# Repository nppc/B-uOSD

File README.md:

# Battery voltage microOSD v1.2
Very small and simple OSD for monitoring Battery voltage. It is useful for AIO micro cameras, FPV helmet etc.

The PCB is very small. Can be ordered at OshPark: https://oshpark.com/shared_projects/nvOy0lBm

## Functionality
- Supports 1S-4S battery monitoring. (Changing onboard voltage divider can be extended for bigger batteries.)
- Adjustable text position.
- Shows current voltage and minimal detected voltage.
- Pilot name, Crosshair and timer.
- Voltage blinking if battery running low.
- Supply voltage 3.3-5.5v.
- Low supply current, no heat generation.
- It is very small size (8.8mm X 6mm).
- Virtually weights nothing.
- Configurable parameters via compiling.

It has minuses too.
- Due to small and slow mcu (no special mcu for signal generation) the OSD picture is not as stable as other bigger OSDs.
- No shadow around the symbols (not visible on white background). Planned it rhe future releases.

Discussion is here: https://www.rcgroups.com/forums/showthread.php?2985720-uOSD-World-smallest-micro-OSD

Some screenshots:

## Connection
There is many possibilities to use this OSD.
One example for 1S setup:

Another example for AIO combo camera/vtx 1S setup:

## Compilation
To compile source files there is several options.
### Under Linux (even cheap OrangePi board will work)
Install `avra` and `git`
```
apt-get install avra git
```
Clone the project to any directory
```
git clone https://github.com/nppc/B-uOSD.git
```
Navigate to `Bin` directory
```
cd B-uOSD/Bin
```
And run `compile_linux.sh` script
```
./compile_linux.sh
```
Now you have .hex file.

### Under Windows
Project can be compiled with AVRASM2 (similar to avra on Linux) or with AVR Studio.

## Flashing
Use `avrdude` software and `USBASP` dongle for flashing microcontroller. 

```
avrdude.exe -c usbasp -p t13 -P usb -B 4.0 -U flash:w:B-uOSD_vXX.hex:a
```

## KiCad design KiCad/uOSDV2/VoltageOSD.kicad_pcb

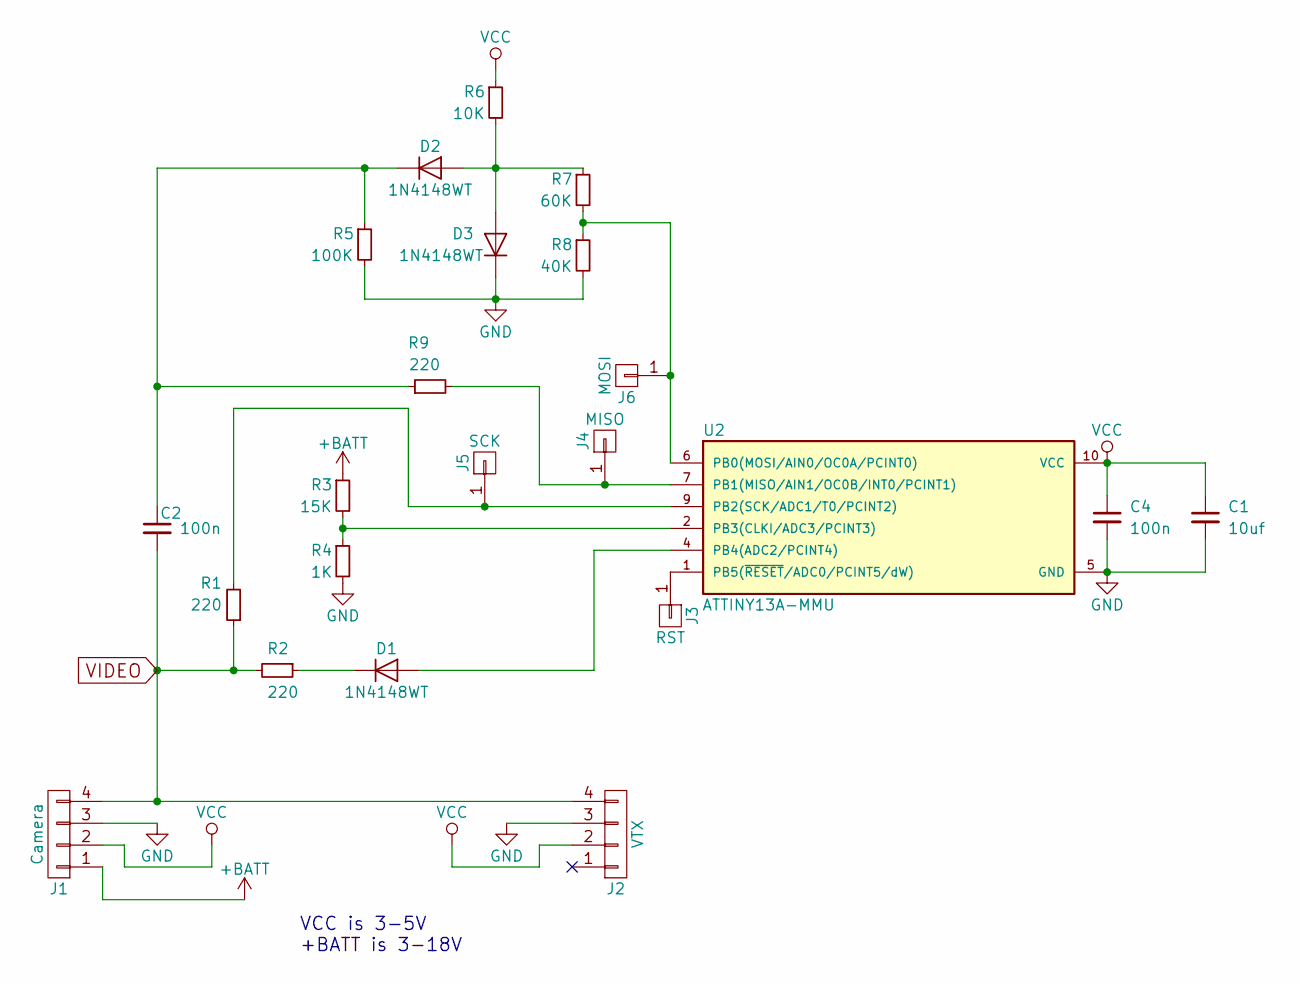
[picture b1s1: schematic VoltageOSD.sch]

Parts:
C1: 10uf; C_0402_NoSilk
C2, C4: 100n; C_0402_NoSilk
D1, D2, D3: 1N4148WT; D_SOD-523
J1: Camera; 4pin_SMD_small
J2: VTX; 4pin_SMD_small
J3: RST; Prog_pad
J4: MISO; Prog_pad
J5: SCK; Prog_pad
J6: MOSI; Prog_pad
R1, R2, R9: 220; R_0402_NoSilk
R3: 15K; R_0402_NoSilk
R4: 1K; R_0402_NoSilk
R5: 100K; R_0402_NoSilk
R6: 10K; R_0402_NoSilk
R7: 60K; R_0402_NoSilk
R8: 40K; R_0402_NoSilk
U2: ATTINY13A-MMU; MLF_10M1

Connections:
+BATT: J1.1, R3.1
GND: C1.2, C4.2, D3.1 (K), J1.3, J2.3, R4.2, R5.2, R8.2, U2.5 (GND)
unnamed: C2.1, D2.1 (K), R5.1, R9.1
unnamed: D1.1 (K), R2.1
unnamed: D1.2 (A), U2.4 (PB4(ADC2/PCINT4))
unnamed: D2.2 (A), D3.2 (A), R6.2, R7.1
unnamed: J3.1, U2.1 (PB5(~RESET~/ADC0/PCINT5/dW))
unnamed: J4.1, R9.2, U2.7 (PB1(MISO/AIN1/OC0B/INT0/PCINT1))
unnamed: J5.1, R1.2, U2.9 (PB2(SCK/ADC1/T0/PCINT2))
unnamed: J6.1, R7.2, R8.1, U2.6 (PB0(MOSI/AIN0/OC0A/PCINT0))
unnamed: R3.2, R4.1, U2.2 (PB3(CLKI/ADC3/PCINT3))
VCC: C1.1, C4.1, J1.2, J2.2, R6.1, U2.10 (VCC)
VIDEO: C2.2, J1.4, J2.4, R1.1, R2.2

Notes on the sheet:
VCC is 3-5V +BATT is 3-18V

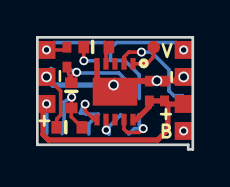
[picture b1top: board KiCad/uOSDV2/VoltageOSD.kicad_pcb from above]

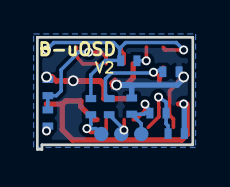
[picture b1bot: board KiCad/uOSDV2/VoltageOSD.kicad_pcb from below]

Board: 2 copper layers, 8.6 x 6.2 mm, 22 parts (12 on the bottom side), 13 nets.

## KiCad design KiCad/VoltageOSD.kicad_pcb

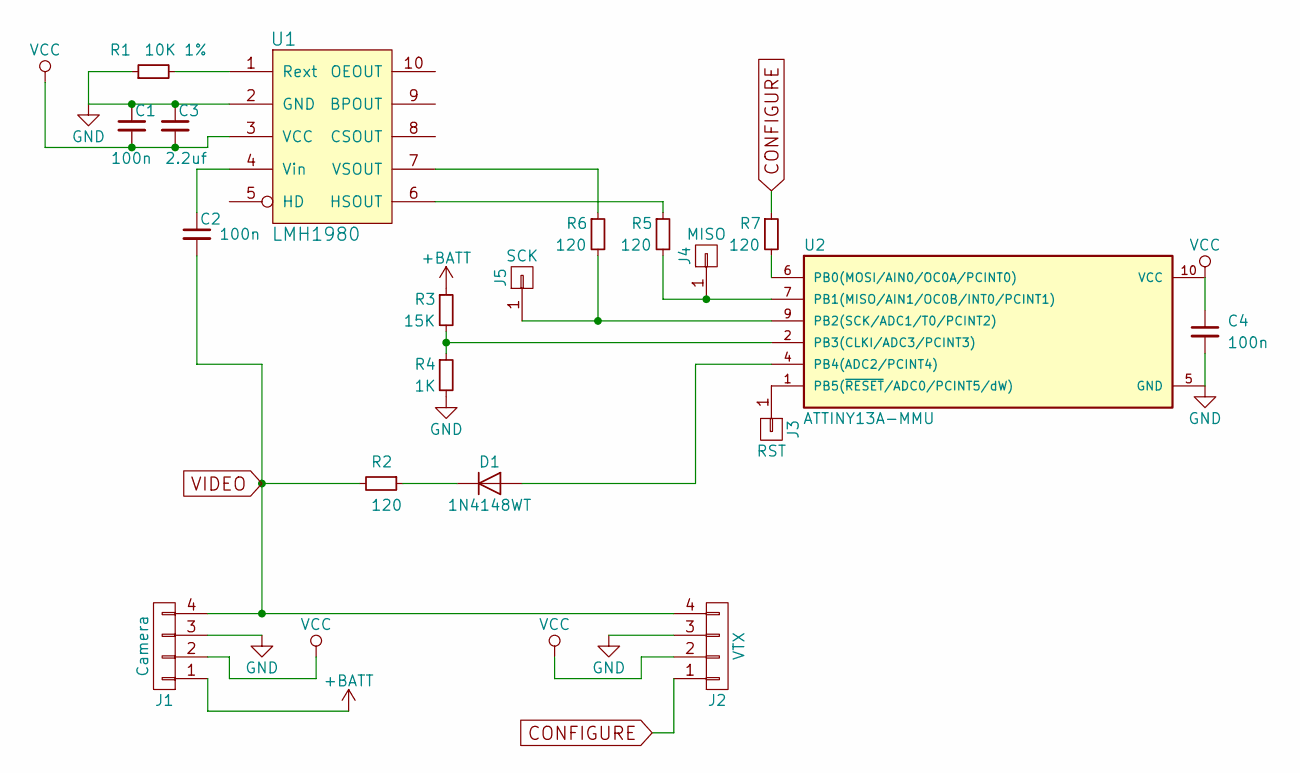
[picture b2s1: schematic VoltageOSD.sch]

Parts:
C1, C2, C4: 100n; C_0402_NoSilk
C3: 2.2uf; C_0603
D1: 1N4148WT; D_SOD-523
J1: Camera; 4pin_SMD_small
J2: VTX; 4pin_SMD_small
J3: RST; Prog_pad
J4: MISO; Prog_pad
J5: SCK; Prog_pad
R1: 10K 1%; R_0402_NoSilk
R2, R5, R6, R7: 120; R_0402_NoSilk
R3: 15K; R_0402_NoSilk
R4: 1K; R_0402_NoSilk
U1: LMH1980; MSOP-10_3x3mm_Pitch0.5mm
U2: ATTINY13A-MMU; MLF_10M1

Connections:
+BATT: J1.1, R3.1
CONFIGURE: J2.1, R7.1
GND: C1.1, C3.1, C4.2, J1.3, J2.3, R1.1, R4.2, U1.2 (GND), U2.5 (GND), U2.11
unnamed: C2.1, U1.4 (Vin)
unnamed: D1.1 (K), R2.1
unnamed: D1.2 (A), U2.4 (PB4(ADC2/PCINT4))
unnamed: J3.1, U2.1 (PB5(~RESET~/ADC0/PCINT5/dW))
unnamed: J4.1, R5.2, U2.7 (PB1(MISO/AIN1/OC0B/INT0/PCINT1))
unnamed: J5.1, R6.2, U2.9 (PB2(SCK/ADC1/T0/PCINT2))
unnamed: R1.2, U1.1 (Rext)
unnamed: R3.2, R4.1, U2.2 (PB3(CLKI/ADC3/PCINT3))
unnamed: R5.1, U1.6 (HSOUT)
unnamed: R6.1, U1.7 (VSOUT)
unnamed: R7.2, U2.6 (PB0(MOSI/AIN0/OC0A/PCINT0))
VCC: C1.2, C3.2, C4.1, J1.2, J2.2, U1.3 (VCC), U2.10 (VCC)
VIDEO: C2.2, J1.4, J2.4, R2.2

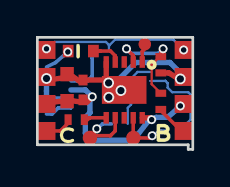
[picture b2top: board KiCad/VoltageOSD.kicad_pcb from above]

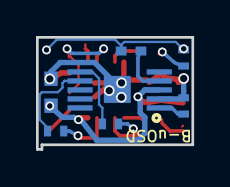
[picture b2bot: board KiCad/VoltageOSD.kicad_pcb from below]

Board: 2 copper layers, 8.6 x 6.2 mm, 19 parts (7 on the bottom side), 16 nets.

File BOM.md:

## Bill of Materials

Symbol | Component | Package | Mouser Part No
---- | ------------ | ------------ | ------------
U1 | LMH1980 | VSSOP-10 | 926-LMH1980MM/NOPB
U2 | ATTINY13A-MMU | MLF-10 | 556-ATTINY13A-MMU
R1 | 10K 1% | SMD 0402 | 603-AF0402FR-0710KL
R2 | 220 | SMD 0402 | 667-ERJ-2RKF2200X
R3 | 15K | SMD 0402 | 652-CR0402FX-1502GLF
R4 | 1K | SMD 0402 | 603-RC0402FR-071KL
R5 | 120 | SMD 0402 | 71-CRCW0402120RFKED
R6 | 120 | SMD 0402 | 71-CRCW0402120RFKED
R7 | 120 | SMD 0402 | 71-CRCW0402120RFKED
C1 | 100n | SMD 0402 | 710-885012105016
C2 | 100n | SMD 0402 | 710-885012105016
C3 | 2.2uf | SMD 0603 | 581-0201ZD225MAT2A
C4 | 100n | SMD 0402 | 710-885012105016
D1 | 1N4148WT | SMD SOD-523 | 512-1N4148WT

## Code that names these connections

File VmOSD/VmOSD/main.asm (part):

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.EQU	BUFFER_LEN	 		= 10	; Length of the SRAM buffers fro text printing. - don't change this...

										
.EQU	VSOUT_PIN	= PB2	; Vertical sync pin
.EQU	HSOUT_PIN	= PB1	; Horizontal sync pin (Seems CSOUT pin is more reliable)
.EQU	CONF_PIN	= PB0	; Pin for device Configuration
.EQU	VBAT_PIN	= PB3	; Resistor divider (15K/1K) for voltage measurement (4S max)
.EQU	VIDEO_PIN	= PB4	; OSD Video OUT

.def	z0			=	r0
.def	z1			=	r1
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		out CLKPR, tmp		; enable clock change
		out CLKPR, z0		; prescaler 1
		
		; Configure Video pin as OUTPUT (LOW)
		sbi	DDRB, VIDEO_PIN
		; Enable pullup on Configure Pin. We will enter configure mode if this pin will go LOW (by PCINT interrupt)
		sbi	PORTB, CONF_PIN
		
		;initialize INT0 
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
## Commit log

2017-06-04 change schematic for INT0. Add ASM project.
2017-06-04 Ready for testing alfa code
2017-06-05 Added ADC and software UART routines. Needs testing...
2017-06-05 UART routines tested and working. Baud is 19200
2017-06-06 Proccessing Commands, PART1
2017-06-06 TV out partially working, but only 7 lines of char printed.
2017-06-07 Discard using Timer for printing. It is just wasete of resources.
2017-06-07 Added EEPROM and WATCHDOG routines. Some optimizations. Everything needs testing...
2017-06-07 Correct syntax error
2017-06-07 Introduced Vertical Symbol Stretching
2017-06-07 First working version. Mostly tested.
2017-06-07 Code polish
2017-06-08 .gitignore added
2017-06-08 Final Schematic and PCB (sent to OshPark)
2017-06-08 Readme added
2017-06-08 Fonts redesigned. Now they are variable width (experimental).
2017-06-08 Introduce Overclocking (experimental).
2017-06-08 GPL header is added to the files
2017-06-08 Added Voltage correction functionality.
2017-06-08 Small syntax fix. Overclocked to 11.5mhz
2017-06-09 Some changes to the schematic values. Added space after bitmap.
2017-06-09 Images update
2017-06-09 Font - new version
2017-06-09 Disable overclock in Configuration mode.
2017-06-09 Implement store/restore settings from EEPROM
2017-06-09 Low Battery blink implemented. Needs testing.
2017-06-09 V1.0 Release. Seems everything is working.
2017-06-09 Defaults changed. Hex file uploaded.
2017-06-09 More Overclock, Small code optimization for size.
2017-06-10 OSD is more stable now. Some flash size optimizations.
2017-06-11 New 7bit font. Flash size optimizations.
2017-06-12 Compatibility with cmd assemblers (AVRA, AVRASM2).
2017-06-12 Connections images added
2017-06-12 Finished changes for V1.1
2017-06-13 Screenshots from v1.1 added
2017-06-28 Try fit code for printing second voltage
2017-06-28 Try fit code for printing second voltage (PART 2)
2017-06-28 Different font size for 1st and 2nd voltages. Code optimization for size.
2017-06-28 change compile scripts
2017-07-31 Added AIO image
2017-07-31 Add AIO Image
2017-07-31 Added more images
2017-07-31 Adjusted schematic and PCB (not critical values)
2017-07-31 Success on 2 voltages project!
2017-08-01 Conditional compilation fix. New image added.
2017-08-01 Readme adjusted
2017-08-01 Readme advanced to 1.2 version
2017-08-01 Added old fassion square font
2017-08-01 Minor fixes to font rendering on OSD
2017-08-03 OshPark link
2017-08-09 Added BOM.txt draft
2017-08-10 Freeup some FLASH and startup delay for proper min voltage measuring
2017-08-10 BOM updated with Mouser part numbers
2017-08-10 Fix problem with jumping Bitmap while blinking
2017-08-10 Compiled V1.2 with latest fixes
2017-08-11 Photo updated
2017-08-11 Fix for min_voltage update at startup.
2017-08-11 Upload fixed hex files for V1.2
2017-08-11 Fixed bug with unstable output if 0 digit exist in the number
2017-08-16 Can now Enable/Disable configuration functionality
2017-08-16 Alfa version of PILOTNAME feature implementation
2017-08-16 fix compilation errors. PILOTNAME feature implemented.
2017-08-16 Added other letters from alphabet.
2017-08-17 Fixed bug with PILOTNAME chars addressing
2017-08-17 Sample PILOTNAME image added
2017-08-25 V2.0 Full rework of code for better flexibility. Serial configuration is dropped.
2017-08-25 Adjust compile script
2017-08-25 Fix small bug, adjust compile/flash script
2017-08-25 Crosshair added. Timer (experimental)
2017-08-25 Small fix, V2.0 is working!
2017-08-29 Uodate Readme for V2.0
2017-10-19 Fix small bug in ADC reading
2017-11-09 Added link to RCG
2017-11-13 Added configuration explanation comments
2017-11-29 Preparing for the V2 PCB version without LMH IC
2017-11-29 Start drafting firmware side
2017-12-04 parts placement
2017-12-11 Changed 2.2uf capacitor to 0402 10uf
2017-12-11 Changed 2.2uf capacitor to 0603 10uf
2017-12-14 Datasheet for attiny84a
2017-12-21 first draft version of firmware without video chip
2017-12-21 cleanup
2017-12-21 First compilation of V2
2017-12-25 V2 PCB componnts placement
2017-12-26 Added auto calibration for better video sync timing
2017-12-26 New test version with adaptive timing
2018-01-05 Output SYNC singgnal (ANACOMP) to the SCK (PB2) pin
2018-01-05 Compile test version
2018-01-11 Add some more debug logic
2018-01-11 Compiled debug version
2018-01-11 Remove is_h_sync variable. Add more debug code
2018-01-11 Preserve Pins state while drawing OSD text. Mostly for debug purposes.
2018-01-11 fix typo for PORTB in TVOUT
2018-01-12 Fixed wierd bug in OCR0A calibration.
2018-01-12 First working V2 without sync MCU
2018-03-26 Added avrasm2 to bin
2018-10-29 BOM for V2 board
2019-02-12 V2 images

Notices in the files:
VmOSD/VmOSD/main.asm:
B-uOSD is free software: you can redistribute it and/or modify
it under the terms of the GNU General Public License as published by
the Free Software Foundation, either version 3 of the License, or
(at your option) any later version.
